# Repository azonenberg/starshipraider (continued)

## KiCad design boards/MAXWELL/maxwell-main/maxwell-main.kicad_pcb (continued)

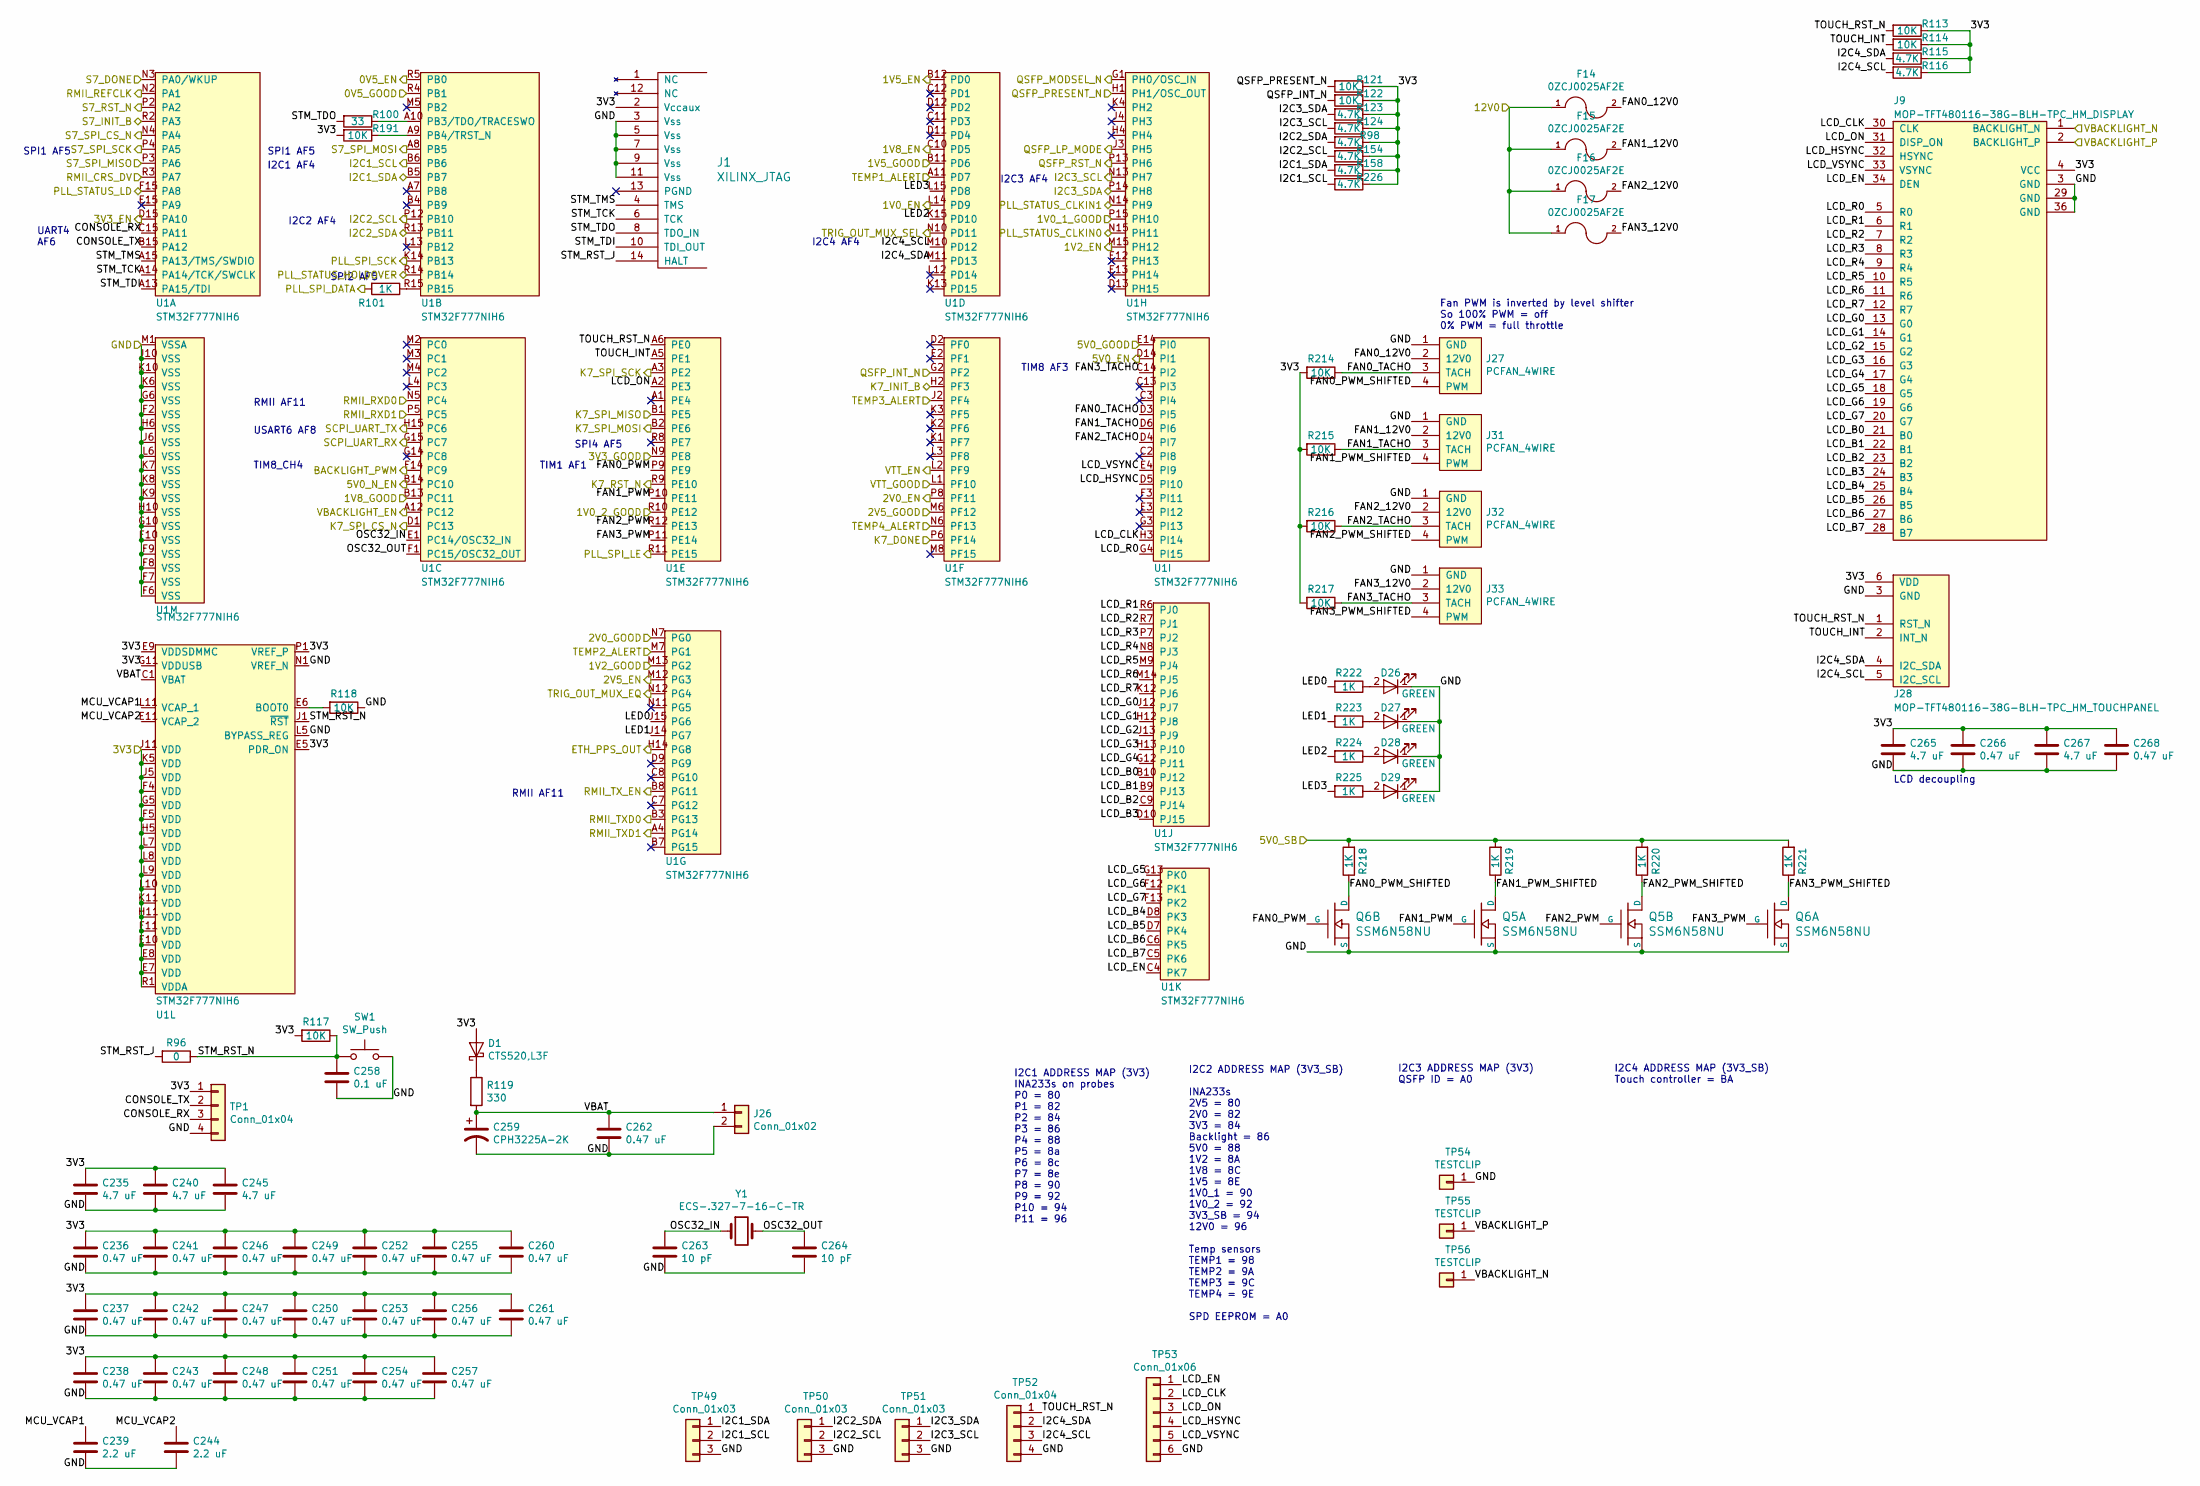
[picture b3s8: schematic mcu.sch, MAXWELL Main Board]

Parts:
C235, C240, C245, C265, C267: 4.7 uF; EIA_0603_CAP_NOSILK
C236, C237, C238, C241, C242, C243, C246, C247, C248, C249, C250, C251, C252, C253, C254, C255, C256, C257, C260, C261, C262, C266, C268: 0.47 uF; EIA_0402_CAP_NOSILK
C239, C244: 2.2 uF; EIA_0603_CAP_NOSILK
C258: 0.1 uF; EIA_0402_CAP_NOSILK
C259: CPH3225A-2K; CAP_SEIKO_CPH3225A
C263, C264: 10 pF; EIA_0402_CAP_NOSILK
D1: CTS520,L3F; SOD882
D26, D27, D28, D29: GREEN; EIA_0603_LED
F14, F15, F16, F17: 0ZCJ0025AF2E; EIA_1206_FUSE_NOSILK
J1: XILINX_JTAG; XILINX_JTAG_PTH_MOLEX_0878311420
J9: MOP-TFT480116-38G-BLH-TPC_HM_DISPLAY; CONN_FFC_0.5MM_1x40_H125755CT-ND
J26: Conn_01x02; CONN_HEADER_2.54MM_1x2
J27, J31, J32, J33: PCFAN_4WIRE; CONN_MOLEX_KK_22-23-2041
J28: MOP-TFT480116-38G-BLH-TPC_HM_TOUCHPANEL; CONN_FFC_0.5MM_1x6_H125773CT-ND
Q5, Q6: SSM6N58NU; DFN_6_0.65MM_2x2MM_GDS
R96: 0; EIA_0402_RES_NOSILK
R98, R115, R116, R123, R124, R154, R158, R226: 4.7K; EIA_0402_RES_NOSILK
R100: 33; EIA_0402_RES_NOSILK
R101, R218, R219, R220, R221, R222, R223, R224, R225: 1K; EIA_0402_RES_NOSILK
R113, R114, R117, R118, R121, R122, R191, R214, R215, R216, R217: 10K; EIA_0402_RES_NOSILK
R119: 330; EIA_0402_RES_NOSILK
SW1: SW_Push; SWITCH_RAFI_MICON_5
TP1, TP52: Conn_01x04; CONN_HEADER_2.54MM_1x4
TP49, TP50, TP51: Conn_01x03; CONN_HEADER_2.54MM_1x3
TP53: Conn_01x06; CONN_HEADER_2.54MM_1x6
TP54, TP55, TP56: TESTCLIP; TESTPOINT_SMT_KEYSTONE_5016
U1: STM32F777NIH6; BGA_216_13x13_DEPOP3x3_0.8MM
Y1: ECS-.327-7-16-C-TR; CRYSTAL_1.6x1.0MM

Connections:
/3V3_SB: C235.1, C236.1, C237.1, C238.1, C240.1, C241.1, C242.1, C243.1, C245.1, C246.1, C247.1, C248.1, C249.1, C250.1, C251.1, C252.1, C253.1, C254.1, C255.1, C256.1, C257.1, C260.1, C261.1, C265.1, C266.1, C267.1, C268.1, D1.2 (A), J1.2 (Vccaux), J9.4 (VCC), J28.6 (VDD), R98.1, R113.1, R114.1, R115.1, R116.1, R117.2, R121.1, R122.1, R123.1, R124.1, R154.1, R158.1, R191.2, R214.2, R215.2, R216.2, R217.2, R226.1, TP1.1, U1.E5 (PDR_ON), U1.E7 (VDD), U1.E8 (VDD), U1.E9 (VDDSDMMC), U1.E10 (VDD), U1.F4 (VDD), U1.F5 (VDD), U1.F11 (VDD), U1.G5 (VDD), U1.G11 (VDDUSB), U1.H5 (VDD), U1.H11 (VDD), U1.J5 (VDD), U1.J11 (VDD), U1.K5 (VDD), U1.K11 (VDD), U1.L7 (VDD), U1.L8 (VDD), U1.L9 (VDD), U1.L10 (VDD), U1.P1 (VREF_P), U1.R1 (VDDA); also elsewhere on the board
/5V0_SB: R218.2, R219.2, R220.2, R221.2; also elsewhere on the board
/12V0: F14.1, F15.1, F16.1, F17.1; also elsewhere on the board
/GND: C235.2, C236.2, C237.2, C238.2, C239.2, C240.2, C241.2, C242.2, C243.2, C244.2, C245.2, C246.2, C247.2, C248.2, C249.2, C250.2, C251.2, C252.2, C253.2, C254.2, C255.2, C256.2, C257.2, C258.2, C259.2, C260.2, C261.2, C262.2, C263.2, C264.2, C265.2, C266.2, C267.2, C268.2, D26.1 (K), D27.1 (K), D28.1 (K), D29.1 (K), J1.3 (Vss), J1.5 (Vss), J1.7 (Vss), J1.9 (Vss), J1.11 (Vss), J9.3 (GND), J9.29 (GND), J9.36 (GND), J26.2, J27.1 (GND), J28.3 (GND), J31.1 (GND), J32.1 (GND), J33.1 (GND), Q5.S1 (S), Q5.S2 (S), Q6.S1 (S), Q6.S2 (S), R118.1, SW1.2, TP1.4, TP49.3, TP50.3, TP51.3, TP52.4, TP53.6, TP54.1, U1.F2 (VSS), U1.F6 (VSS), U1.F7 (VSS), U1.F8 (VSS), U1.F9 (VSS), U1.F10 (VSS), U1.G6 (VSS), U1.G10 (VSS), U1.H6 (VSS), U1.H10 (VSS), U1.J6 (VSS), U1.J10 (VSS), U1.K6 (VSS), U1.K7 (VSS), U1.K8 (VSS), U1.K9 (VSS), U1.K10 (VSS), U1.L5 (BYPASS_REG), U1.L6 (VSS), U1.M1 (VSSA), U1.N1 (VREF_N); also elsewhere on the board
/I2C2_SCL: R154.2, TP50.2, U1.P12 (PB10); also elsewhere on the board
/I2C2_SDA: R98.2, TP50.1, U1.R13 (PB11); also elsewhere on the board
/I2C3_SCL: R124.2, TP51.2, U1.N13 (PH7); also elsewhere on the board
/I2C3_SDA: R123.2, TP51.1, U1.P14 (PH8); also elsewhere on the board
/Inputs/I2C1_SCL: R226.2, TP49.2, U1.B6; also elsewhere on the board
/Inputs/I2C1_SDA: R158.2, TP49.1, U1.B5 (PB7); also elsewhere on the board
/Inputs/S7_DONE: U1.N3 (PA0/WKUP); also elsewhere on the board
/Inputs/S7_INIT_B: U1.R2 (PA3); also elsewhere on the board
/Inputs/S7_RST_N: U1.P2 (PA2); also elsewhere on the board
/Inputs/S7_SPI_CS_N: U1.N4 (PA4); also elsewhere on the board
/Inputs/S7_SPI_MISO: U1.P3 (PA6); also elsewhere on the board
/Inputs/S7_SPI_MOSI: U1.A8 (PB5); also elsewhere on the board
/Inputs/S7_SPI_SCK: U1.P4 (PA5); also elsewhere on the board
/K7_DONE: U1.P6 (PF14); also elsewhere on the board
/K7_INIT_B: U1.H2 (PF3); also elsewhere on the board
/K7_RST_N: U1.R9 (PE10); also elsewhere on the board
/MCU/0V5_EN: U1.R5 (PB0); also elsewhere on the board
/MCU/0V5_GOOD: U1.R4 (PB1); also elsewhere on the board
/MCU/1V0_1_GOOD: U1.P15 (PH10); also elsewhere on the board
/MCU/1V0_2_GOOD: U1.R10 (PE12); also elsewhere on the board
/MCU/1V0_EN: U1.L14 (PD9); also elsewhere on the board
/MCU/1V2_EN: U1.M15 (PH12); also elsewhere on the board
/MCU/1V2_GOOD: U1.M13 (PG2); also elsewhere on the board
/MCU/1V5_EN: U1.B12 (PD0); also elsewhere on the board
/MCU/1V5_GOOD: U1.B11 (PD6); also elsewhere on the board
/MCU/1V8_EN: U1.C10 (PD5); also elsewhere on the board
/MCU/1V8_GOOD: U1.B13 (PC11); also elsewhere on the board
/MCU/2V0_EN: U1.P8 (PF11); also elsewhere on the board
/MCU/2V0_GOOD: U1.N7 (PG0); also elsewhere on the board
/MCU/2V5_EN: U1.M12 (PG3); also elsewhere on the board
/MCU/2V5_GOOD: U1.M6 (PF12); also elsewhere on the board
/MCU/3V3_EN: U1.D15 (PA10); also elsewhere on the board
/MCU/3V3_GOOD: U1.N9 (PE8); also elsewhere on the board
/MCU/5V0_EN: U1.D14 (PI1); also elsewhere on the board
/MCU/5V0_GOOD: U1.E14 (PI0); also elsewhere on the board
/MCU/5V0_N_EN: U1.B14 (PC10); also elsewhere on the board
/MCU/BACKLIGHT_PWM: U1.F14 (PC9); also elsewhere on the board
/MCU/CONSOLE_RX: TP1.3, U1.C15 (PA11)
/MCU/CONSOLE_TX: TP1.2, U1.B15 (PA12)
/MCU/ETH_PPS_OUT: U1.H14 (PG8); also elsewhere on the board
/MCU/FAN0_12V0: F14.2, J27.2 (12V0)
/MCU/FAN0_PWM: Q6.G2 (G), U1.P9 (PE9)
/MCU/FAN0_PWM_SHIFTED: J27.4 (PWM), Q6.D2 (D), R218.1
/MCU/FAN0_TACHO: J27.3 (TACH), R214.1, U1.D3 (PI5)
/MCU/FAN1_12V0: F15.2, J31.2 (12V0)
/MCU/FAN1_PWM: Q5.G1 (G), U1.P10 (PE11)
/MCU/FAN1_PWM_SHIFTED: J31.4 (PWM), Q5.D1 (D), R219.1
/MCU/FAN1_TACHO: J31.3 (TACH), R215.1, U1.D6 (PI6)
/MCU/FAN2_12V0: F16.2, J32.2 (12V0)
/MCU/FAN2_PWM: Q5.G2 (G), U1.R12 (PE13)
/MCU/FAN2_PWM_SHIFTED: J32.4 (PWM), Q5.D2 (D), R220.1
/MCU/FAN2_TACHO: J32.3 (TACH), R216.1, U1.D4 (PI7)
/MCU/FAN3_12V0: F17.2, J33.2 (12V0)
/MCU/FAN3_PWM: Q6.G1 (G), U1.P11 (PE14)
/MCU/FAN3_PWM_SHIFTED: J33.4 (PWM), Q6.D1 (D), R221.1
/MCU/FAN3_TACHO: J33.3 (TACH), R217.1, U1.C14 (PI2)
/MCU/I2C4_SCL: J28.5 (I2C_SCL), R116.2, TP52.3, U1.M10 (PD12)
/MCU/I2C4_SDA: J28.4 (I2C_SDA), R115.2, TP52.2, U1.M11 (PD13)
/MCU/K7_SPI_CS_N: U1.D1 (PC13); also elsewhere on the board
/MCU/K7_SPI_MISO: U1.B1 (PE5); also elsewhere on the board
/MCU/K7_SPI_MOSI: U1.B2 (PE6); also elsewhere on the board
/MCU/K7_SPI_SCK: U1.A3 (PE2); also elsewhere on the board
/MCU/LCD_B0: J9.21 (B0), U1.B10 (PJ12)
/MCU/LCD_B1: J9.22 (B1), U1.B9 (PJ13)
/MCU/LCD_B2: J9.23 (B2), U1.C9 (PJ14)
/MCU/LCD_B3: J9.24 (B3), U1.D10 (PJ15)
/MCU/LCD_B4: J9.25 (B4), U1.D8 (PK3)
/MCU/LCD_B5: J9.26 (B5), U1.D7 (PK4)
/MCU/LCD_B6: J9.27 (B6), U1.C6 (PK5)
/MCU/LCD_B7: J9.28 (B7), U1.C5 (PK6)
/MCU/LCD_CLK: J9.30 (CLK), TP53.2, U1.H3 (PI14)
/MCU/LCD_EN: J9.34 (DEN), TP53.1, U1.C4 (PK7)
/MCU/LCD_G0: J9.13 (G0), U1.J12 (PJ7)
/MCU/LCD_G1: J9.14 (G1), U1.H12 (PJ8)
/MCU/LCD_G2: J9.15 (G2), U1.J13 (PJ9)
/MCU/LCD_G3: J9.16 (G3), U1.H13 (PJ10)
/MCU/LCD_G4: J9.17 (G4), U1.G12 (PJ11)
/MCU/LCD_G5: J9.18 (G5), U1.G13 (PK0)
/MCU/LCD_G6: J9.19 (G6), U1.F12 (PK1)
/MCU/LCD_G7: J9.20 (G7), U1.F13 (PK2)
/MCU/LCD_HSYNC: J9.32 (HSYNC), TP53.4, U1.D5 (PI10)
/MCU/LCD_ON: J9.31 (DISP_ON), TP53.3, U1.A2 (PE3)
/MCU/LCD_R0: J9.5 (R0), U1.G4 (PI15)
/MCU/LCD_R1: J9.6 (R1), U1.R6 (PJ0)
/MCU/LCD_R2: J9.7 (R2), U1.R7 (PJ1)
/MCU/LCD_R3: J9.8 (R3), U1.P7 (PJ2)
/MCU/LCD_R4: J9.9 (R4), U1.N8 (PJ3)
/MCU/LCD_R5: J9.10 (R5), U1.M9 (PJ4)
/MCU/LCD_R6: J9.11 (R6), U1.M14 (PJ5)
/MCU/LCD_R7: J9.12 (R7), U1.K12 (PJ6)
/MCU/LCD_VSYNC: J9.33 (VSYNC), TP53.5, U1.E4 (PI9)
/MCU/LED0: R222.2, U1.J15 (PG6)
/MCU/LED1: R223.2, U1.J14 (PG7)
/MCU/LED2: R224.2, U1.K15 (PD10)
/MCU/LED3: R225.2, U1.L15 (PD8)
/MCU/MCU_VCAP1: C239.1, U1.L11 (VCAP_1)
/MCU/MCU_VCAP2: C244.1, U1.E11 (VCAP_2)
/MCU/OSC32_IN: C263.1, U1.E1 (PC14/OSC32_IN), Y1.1
/MCU/OSC32_OUT: C264.1, U1.F1 (PC15/OSC32_OUT), Y1.2
/MCU/RMII_CRS_DV: U1.R3 (PA7); also elsewhere on the board
/MCU/RMII_REFCLK: U1.N2 (PA1); also elsewhere on the board
/MCU/RMII_RXD0: U1.N5 (PC4); also elsewhere on the board
/MCU/RMII_RXD1: U1.P5 (PC5); also elsewhere on the board
/MCU/RMII_TXD0: U1.B3 (PG13); also elsewhere on the board
/MCU/RMII_TXD1: U1.A4 (PG14); also elsewhere on the board
/MCU/RMII_TX_EN: U1.B8 (PG11); also elsewhere on the board
/MCU/STM_RST_J: J1.14 (HALT), R96.2
/MCU/STM_RST_N: C258.1, R96.1, R117.1, SW1.1, U1.J1 (~RST)
/MCU/STM_TCK: J1.6 (TCK), U1.A14 (PA14/TCK/SWCLK)
/MCU/STM_TDI: J1.10 (TDI_OUT), U1.A13 (PA15/TDI)
/MCU/STM_TDO: J1.8 (TDO_IN), R100.2
/MCU/STM_TMS: J1.4 (TMS), U1.A15 (PA13/TMS/SWDIO)
/MCU/TOUCH_INT: J28.2 (INT_N), R114.2, U1.A5 (PE1)
/MCU/TOUCH_RST_N: J28.1 (RST_N), R113.2, TP52.1, U1.A6 (PE0)
/MCU/VBACKLIGHT_EN: U1.A12 (PC12); also elsewhere on the board
/MCU/VBAT: C259.1, C262.1, J26.1, R119.2, U1.C1 (VBAT)
/MCU/VTT_EN: U1.L2 (PF9); also elsewhere on the board
/MCU/VTT_GOOD: U1.L1 (PF10); also elsewhere on the board
/PLL_SPI_CLK: U1.K14 (PB13); also elsewhere on the board
/PLL_SPI_DATA: R101.2; also elsewhere on the board
/PLL_SPI_LE: U1.R11 (PE15); also elsewhere on the board
/PLL_STATUS_CLKIN0: U1.N15 (PH11); also elsewhere on the board
/PLL_STATUS_CLKIN1: U1.N14 (PH9); also elsewhere on the board
/PLL_STATUS_HOLDOVER: U1.R14 (PB14); also elsewhere on the board
/PLL_STATUS_LD: U1.F15 (PA8); also elsewhere on the board
/QSFP_INT_N: R122.2, U1.G2 (PF2); also elsewhere on the board
/QSFP_LP_MODE: U1.J3 (PH5); also elsewhere on the board
/QSFP_MODSEL_N: U1.G1 (PH0/OSC_IN); also elsewhere on the board
/QSFP_PRESENT_N: R121.2, U1.H1 (PH1/OSC_OUT); also elsewhere on the board
/QSFP_RST_N: U1.P13 (PH6); also elsewhere on the board
/SCPI_UART_RX: U1.G15 (PC7); also elsewhere on the board
/SCPI_UART_TX: U1.H15 (PC6); also elsewhere on the board
/TEMP1_ALERT: U1.A11 (PD7); also elsewhere on the board
/TEMP2_ALERT: U1.M7 (PG1); also elsewhere on the board
/TEMP3_ALERT: U1.J2 (PF4); also elsewhere on the board
/TEMP4_ALERT: U1.N6 (PF13); also elsewhere on the board
/TRIG_OUT_MUX_EQ: U1.N12 (PG4); also elsewhere on the board
/TRIG_OUT_SEL: U1.N10 (PD11); also elsewhere on the board
/VBACKLIGHT_N: J9.1 (BACKLIGHT_N), TP56.1; also elsewhere on the board
/VBACKLIGHT_P: J9.2 (BACKLIGHT_P), TP55.1; also elsewhere on the board
unnamed: D1.1 (K), R119.1
unnamed: D26.2 (A), R222.1
unnamed: D27.2 (A), R223.1
unnamed: D28.2 (A), R224.1
unnamed: D29.2 (A), R225.1
unnamed: R100.1, U1.A10 (PB3/TDO/TRACESWO)
unnamed: R101.1, U1.R15 (PB15)
unnamed: R118.2, U1.E6 (BOOT0)
unnamed: R191.1, U1.A9 (PB4/TRST_N)

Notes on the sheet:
SPI1 AF5
SPI2 AF5
I2C1 AF4
I2C2 AF4
I2C4 AF4
LCD decoupling
UART4 AF6
USART6 AF8
I2C3 AF4
I2C2 ADDRESS MAP (3V3_SB) INA233s 2V5 = 80 2V0 = 82 3V3 = 84 Backlight = 86 5V0 = 88 1V2 = 8A 1V8 = 8C 1V5 = 8E 1V0_1 = 90 1V0_2 = 92 3V3_SB = 94 12V0 = 96 Temp sensors TEMP1 = 98 TEMP2 = 9A TEMP3 = 9C TEMP4 = 9E SPD EEPROM = A0
I2C3 ADDRESS MAP (3V3) QSFP ID = A0
I2C4 ADDRESS MAP (3V3_SB) Touch controller = BA
TIM8_CH4
I2C1 ADDRESS MAP (3V3) INA233s on probes P0 = 80 P1 = 82 P2 = 84 P3 = 86 P4 = 88 P5 = 8a P6 = 8c P7 = 8e P8 = 90 P9 = 92 P10 = 94 P11 = 96
RMII AF11
SPI4 AF5
TIM1 AF1
TIM8 AF3
Fan PWM is inverted by level shifter So 100% PWM = off 0% PWM = full throttle

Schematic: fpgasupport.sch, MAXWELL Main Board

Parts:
C137, C144: 330 uF; EIA_1210_CAP_NOSILK
C138, C142, C143: 100 uF; EIA_1210_CAP_NOSILK
C139, C140, C146: 47 uF; EIA_0805_CAP_NOSILK
C141: 47 uF; EIA_1210_CAP_NOSILK
C145, C147, C148, C149, C150, C151, C152, C153, C154, C158, C159, C160, C164: 4.7 uF; EIA_0603_CAP_NOSILK
C155, C156, C157, C161, C162, C163: 22 uF; EIA_0805_CAP_NOSILK
C165: 0.47 uF; EIA_0402_CAP_NOSILK
FB22, FB23, FB24: 300R; EIA_2220_INDUCTOR
J10: XILINX_JTAG; XILINX_JTAG_PTH_MOLEX_0878311420
R54, R55, R57, R58, R59, R60, R61: 33; EIA_0402_RES_NOSILK
R56, R245, R246, R247: 4.7K; EIA_0402_RES_NOSILK
TP57, TP58, TP59, TP60, TP61, TP62, TP63, TP64, TP65, TP66, TP67, TP68, TP69, TP70, TP71, TP72, TP73: TESTCLIP; TESTPOINT_SMT_KEYSTONE_5016
TP74, TP75, TP76: TESTPAD; TESTPOINT_SMT_0.5MM
U2: XC7K160T-2FFG676C; BGA_676_27x27_FULLARRAY_1MM_FFG676
U34: S25FL128LAGNFV010; DFN_8_1.27MM_6x5MM

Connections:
/1V0_1: C137.1, C138.1, C144.1, C145.1, C147.1, C148.1, TP57.1, U2.J9 (VCCINT), U2.K8 (VCCINT), U2.K10 (VCCINT), U2.K12 (VCCINT), U2.K14 (VCCINT), U2.L9 (VCCINT), U2.L13 (VCCINT), U2.L15 (VCCINT), U2.M8 (VCCINT), U2.M14 (VCCINT), U2.N9 (VCCINT), U2.N13 (VCCBRAM), U2.N15 (VCCINT), U2.P14 (VCCINT), U2.R13 (VCCBRAM), U2.R15 (VCCINT), U2.T12 (VCCBRAM), U2.T14 (VCCINT), U2.U13 (VCCBRAM), U2.U15 (VCCINT); also elsewhere on the board
/1V0_2: C155.1, C158.1, FB22.2; also elsewhere on the board
/1V2: C156.1, C159.1, FB23.2, TP66.1; also elsewhere on the board
/1V5: C142.1, TP60.1, U2.AA1 (VCCO_34), U2.AA11 (VCCO_33), U2.AB8 (VCCO_33), U2.AB18 (VCCO_32), U2.AC5 (VCCO_34), U2.AC15 (VCCO_32), U2.AD2 (VCCO_34), U2.AD12 (VCCO_33), U2.AE9 (VCCO_33), U2.AE19 (VCCO_32), U2.AF6 (VCCO_34), U2.AF16 (VCCO_32), U2.U3 (VCCO_34), U2.V10 (VCCO_33), U2.W7 (VCCO_33), U2.W17 (VCCO_32), U2.Y4 (VCCO_34), U2.Y14 (VCCO_32); also elsewhere on the board
/1V8: C139.1, C146.1, C157.1, C160.1, FB24.2, TP58.1, TP67.1, U2.E8 (VCCBATT_0), U2.L11 (VCCAUX), U2.M10 (VCCAUX), U2.M12 (VCCADC_0), U2.P10 (VCCAUX), U2.T10 (VCCAUX), U2.U11 (VCCAUX); also elsewhere on the board
/2V0: C140.1, TP59.1, U2.P8 (VCCAUX_IO_G0), U2.R9 (VCCAUX_IO_G0), U2.T8 (VCCAUX_IO_G0); also elsewhere on the board
/2V5: C143.1, TP62.1, U2.A11 (VCCO_16), U2.AA21 (VCCO_12), U2.AC25 (VCCO_12), U2.AD22 (VCCO_12), U2.AF26 (VCCO_12), U2.B8 (VCCO_16), U2.B18 (VCCO_15), U2.C15 (VCCO_16), U2.D12 (VCCO_16), U2.E9 (VCCO_16), U2.E19 (VCCO_15), U2.F16 (VCCO_15), U2.G13 (VCCO_16), U2.H10 (VCCO_16), U2.H20 (VCCO_15), U2.J17 (VCCO_15), U2.K24 (VCCO_13), U2.M18 (VCCO_15), U2.N25 (VCCO_13), U2.P22 (VCCO_13), U2.R19 (VCCO_13), U2.T16 (VCCO_13), U2.T26 (VCCO_13), U2.U23 (VCCO_12), U2.V20 (VCCO_12), U2.Y24 (VCCO_12); also elsewhere on the board
/3V3: C141.1, C164.1, C165.1, J10.2 (Vccaux), R56.1, R57.1, R245.1, R246.1, R247.1, TP61.1, U2.A21 (VCCO_14), U2.C25 (VCCO_14), U2.D22 (VCCO_14), U2.F26 (VCCO_14), U2.G23 (VCCO_14), U2.L7 (VCCO_0), U2.L21 (VCCO_14), U2.P7 (CFGBVS_0), U2.T5 (M0_0), U2.T6 (VCCO_0), U34.8 (VCC); also elsewhere on the board
/FPGA Support/GTX_1V0: C149.1, C152.1, C161.1, FB22.1, TP63.1, U2.C6 (MGTAVCC), U2.E6 (MGTAVCC), U2.G6 (MGTAVCC), U2.J6 (MGTAVCC), U2.L6 (MGTAVCC)
/FPGA Support/GTX_1V8: C151.1, C154.1, C163.1, FB24.1, TP65.1, U2.N6 (MGTVCCAUX)
/FPGA Support/K7_QSPI_SCK: R55.2, U34.6 (CLK)
/FPGA Support/K7_TCK: J10.6 (TCK), U2.L8 (TCK_0)
/FPGA Support/K7_TDI: J10.10 (TDI_OUT), U2.R6 (TDI_0)
/FPGA Support/K7_TDO: J10.8 (TDO_IN), R54.2
/FPGA Support/K7_TMS: J10.4 (TMS), U2.N8 (TMS_0)
/GND: C137.2, C138.2, C139.2, C140.2, C141.2, C142.2, C143.2, C144.2, C145.2, C146.2, C147.2, C148.2, C149.2, C150.2, C151.2, C152.2, C153.2, C154.2, C164.2, C165.2, J10.3 (Vss), J10.5 (Vss), J10.7 (Vss), J10.9 (Vss), J10.11 (Vss), TP68.1, TP69.1, TP70.1, TP71.1, TP72.1, TP73.1, U2.A1 (GND), U2.A2 (GND), U2.A5 (GND), U2.A6 (GND), U2.A7 (GND), U2.A16 (GND), U2.A26 (GND), U2.AA6 (GND), U2.AA16 (GND), U2.AA26 (GND), U2.AB3 (GND), U2.AB13 (GND), U2.AB23 (GND), U2.AC10 (GND), U2.AC20 (GND), U2.AD7 (GND), U2.AD17 (GND), U2.AE4 (GND), U2.AE14 (GND), U2.AE24 (GND), U2.AF1 (GND), U2.AF11 (GND), U2.AF21 (GND), U2.B4 (GND), U2.B7 (GND), U2.B13 (GND), U2.B23 (GND), U2.C1 (GND), U2.C5 (GND), U2.C7 (GND), U2.C10 (GND), U2.C20 (GND), U2.D4 (GND), U2.D7 (GND), U2.D17 (GND), U2.E1 (GND), U2.E2 (GND), U2.E5 (GND), U2.E7 (GND), U2.E14 (GND), U2.E24 (GND), U2.F3 (GND), U2.F4 (GND), U2.F7 (GND), U2.F11 (GND), U2.F21 (GND), U2.G1 (GND), U2.G5 (GND), U2.G8 (GND), U2.G18 (GND), U2.H4 (GND), U2.H7 (GND), U2.H15 (GND), U2.H25 (GND), U2.J1 (GND), U2.J2 (GND), U2.J5 (GND), U2.J12 (GND), U2.J22 (GND), U2.K3 (GND), U2.K4 (GND), U2.K7 (GND), U2.K9 (GND), U2.K11 (GND), U2.K13 (GND), U2.K19 (GND), U2.L1 (GND), U2.L5 (GND), U2.L10 (GND), U2.L12 (GND), U2.L14 (GND), U2.L16 (GND), U2.L26 (GND), U2.M4 (GND), U2.M7 (GND), U2.M9 (GND), U2.M11 (GNDADC_0), U2.M13 (GND), U2.M15 (GND), U2.M23 (GND), U2.N1 (GND), U2.N2 (GND), U2.N5 (GND), U2.N7 (GND), U2.N10 (GND), U2.N11 (VREFN_0), U2.N12 (VP_0), U2.N14 (GND), U2.N20 (GND), U2.P3 (GND), U2.P4 (GND), U2.P5 (M2_0), U2.P9 (GND), U2.P11 (VN_0), U2.P12 (VREFP_0), U2.P13 (GND), U2.P15 (GND), U2.P17 (GND), U2.R1 (GND), U2.R2 (GND), U2.R5 (GND), U2.R8 (GND), U2.R10 (GND), U2.R11 (DXN_0), U2.R12 (DXP_0), U2.R14 (GND), U2.R24 (GND), U2.T1 (GND), U2.T2 (M1_0), U2.T3 (GND), U2.T4 (GND), U2.T9 (GND), U2.T11 (GND), U2.T13 (GND), U2.T15 (GND), U2.T21 (GND), U2.U8 (GND), U2.U10 (GND), U2.U12 (GND), U2.U14 (GND), U2.U18 (GND), U2.V5 (GND), U2.V15 (GND), U2.V25 (GND), U2.W2 (GND), U2.W12 (GND), U2.W22 (GND), U2.Y9 (GND), U2.Y19 (GND), U34.4 (GND); also elsewhere on the board
/GTX_1V2: C150.1, C153.1, C162.1, FB23.1, TP64.1, U2.B3 (MGTAVTT), U2.C2 (MGTAVTT), U2.D3 (MGTAVTT), U2.G2 (MGTAVTT), U2.H3 (MGTAVTT), U2.L2 (MGTAVTT), U2.M3 (MGTAVTT); also elsewhere on the board
/K7_DONE: TP76.1, U2.J7 (DONE_0); also elsewhere on the board
/K7_INIT_B: R56.2, TP74.1, U2.G7 (INIT_B_0); also elsewhere on the board
/K7_QSPI_CS_N: R245.2, U34.1 (CS#); also elsewhere on the board
/K7_QSPI_DQ0: R61.1; also elsewhere on the board
/K7_QSPI_DQ1: R58.2; also elsewhere on the board
/K7_QSPI_DQ2: R59.2, R246.2; also elsewhere on the board
/K7_QSPI_DQ3: R60.1, R247.2; also elsewhere on the board
/K7_RST_N: R57.2, TP75.1, U2.P6 (PROGRAM_B_0); also elsewhere on the board
unnamed: C155.2, C158.2, C161.2
unnamed: C156.2, C159.2, C162.2
unnamed: C157.2, C160.2, C163.2
unnamed: R54.1, U2.R7 (TDO_0)
unnamed: R55.1, U2.C8 (CCLK_0)
unnamed: R58.1, U34.2 (DO/IO1)
unnamed: R59.1, U34.3 (WP#/IO2)
unnamed: R60.2, U34.7 (HOLD#/IO3)
unnamed: R61.2, U34.5 (DI/IO0)

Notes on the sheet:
Total 10 mV p-p max on GTX rails Need filter networks
VCCINT decoupling
VCCBRAM decoupling
VCCAUX decoupling
VCCAUX_IO decoupling
VCCO_0/14 decoupling
VCCO_32/33/34 decoupling
VCCO_12/13/15/16 decoupling
GTX decoupling

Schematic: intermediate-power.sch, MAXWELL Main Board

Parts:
C106: 100 uF 63V; CAP_AL_10MM_SMT
C282: 100 uF 25V; CAP_AL_6.3MM_SMT
C323: 4.7 uF 25V; EIA_0805_CAP_NOSILK
C324: 1 uF; EIA_0603_CAP_NOSILK
C339: 22 uF 25V; EIA_1210_CAP_NOSILK
C340: 22 uF; EIA_0805_CAP_NOSILK
C341: DNP; EIA_1206_CAP_NOSILK
C403, C408: 0.47 uF; EIA_0402_CAP_NOSILK
F13: 10A; EIA_1206_FUSE_NOSILK
FL1: BNX003-11
J24: VES180_MINIFITJR; CONN_MOLEX_MINIFITJR_39-30-1080
R171: 2.2K 1%; EIA_0402_RES_NOSILK
R172: 10K; EIA_0402_RES_NOSILK
R205: LVK12R012FER; OHMITE_LVK12
R206: LVK25R002FER; OHMITE_LVK25
SW2: SW_SPST; CONN_HEADER_2.54MM_1x2
TP2: TESTPAD; TESTPOINT_SMT_0.5MM
U52: E36SC12009NRFA; MODULE_DCDC_DOSA_EIGHTHBRICK
U56: MCP1755S-DFN; DFN_8_0.5MM_2x3MM_TALL
U60: OKL-T/3-W12P-C; MODULE_MURATA_OKL-T3-W12
U79, U84: INA233; SOP_10_0.5MM_3MM

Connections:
/3V3_SB: C403.1, C408.1, R205.2 (Vo), U60.5 (SENSE), U79.6 (Vs+), U79.8 (Vbus), U84.6 (Vs+); also elsewhere on the board
/5V0_SB: C324.1, R172.2, U56.1 (VOUT); also elsewhere on the board
/12V0: C323.1, C339.1, R206.2 (Vo), U52.7 (SENSE+), U56.8 (VIN), U60.1 (EN), U60.2 (VIN), U60.9 (SEQ/TRK), U84.8 (Vbus); also elsewhere on the board
/GND: C106.2, C282.2, C323.2, C324.2, C339.2, C340.2, C341.2, C403.2, C408.2, FL1.4 (GND_OUT), R171.2, SW2.1 (A), U52.3 (GND_IN), U52.4 (GND_OUT), U52.5 (SENSE-), U56.4 (GND), U56.PAD (GND), U60.3 (GND), U60.7 (GND), U79.7 (GND), U84.7 (GND); also elsewhere on the board
/I2C2_SCL: U79.5 (SCL), U84.2 (A0), U84.5 (SCL); also elsewhere on the board
/I2C2_SDA: U79.1 (A1), U79.2 (A0), U79.4 (SDA), U84.1 (A1), U84.4 (SDA); also elsewhere on the board
/Power Supply/Intermediate and Standby Rails/3V3_SB_GOOD: R172.1, TP2.1, U60.10 (PGOOD)
/Power Supply/Intermediate and Standby Rails/3V3_SB_SENSE_HI: R205.3 (Ihi), U79.10 (Vin+)
/Power Supply/Intermediate and Standby Rails/3V3_SB_SENSE_LO: R205.1 (Ilo), U79.9 (Vin-)
/Power Supply/Intermediate and Standby Rails/12V0_ON_N: SW2.2 (B), U52.2 (ON/OFF)
/Power Supply/Intermediate and Standby Rails/12V0_SENSE_HI: R206.3 (Ihi), U84.10 (Vin+)
/Power Supply/Intermediate and Standby Rails/12V0_SENSE_LO: R206.1 (Ilo), U84.9 (Vin-)
/Power Supply/Intermediate and Standby Rails/GND_IN: FL1.3 (GND_IN), J24.1 (GND), J24.2 (GND), J24.3 (GND), J24.4 (GND)
/Power Supply/Intermediate and Standby Rails/VIN: F13.1, J24.5 (VIN), J24.6 (VIN), J24.7 (VIN), J24.8 (VIN)
/Power Supply/Intermediate and Standby Rails/VIN_FILT: C106.1, FL1.2 (PWR_OUT), U52.1 (VIN)
/Power Supply/Intermediate and Standby Rails/VIN_FUSED: F13.2, FL1.1 (PWR_IN)
unnamed: C282.1, R206.4 (Vi), U52.8 (VOUT)
unnamed: C340.1, C341.1, R205.4 (Vi), U60.4 (VOUT)
unnamed: R171.1, U60.6 (TRIM)

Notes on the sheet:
Input is 24V @ 4A or 48V @ 2A. Use 10A fuse to provide some headroom Supply recommends more like 20 for inrush though?
Expected efficiency @ 48V in is ~~93%. Assuming 7.3A load, we'll dissipate a bit under 7W in this module. Overcurrent shutdown at around 11A Converter is isolated, but in/out ground are connected since we don't actually need isolation.
Hard power switch (back side)
5V standby rail is just used to drive enable lines for DC-DC's Doesn't need high current
8'h94
12 mR = 18 mV @ 1.5A 208.333 uA/LSB
8'h96
2 mR = 16 mV @ 8A 1.25 mA/LSB

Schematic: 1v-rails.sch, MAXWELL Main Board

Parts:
C283, C297, C298, C299, C300, C301, C302, C303, C304, C305, C306, C307: 22 uF; EIA_1210_CAP_NOSILK
C308, C309, C310, C311, C312, C313, C314, C315, C316, C317, C318, C319: 47 uF; EIA_1206_CAP_NOSILK
C320, C321, C322, C334: 0.1 uF; EIA_0402_CAP_NOSILK
C325, C326: 22 uF 25V; EIA_1210_CAP_NOSILK
C327, C328: 22 uF; EIA_0805_CAP_NOSILK
C329, C330: DNP; EIA_1206_CAP_NOSILK
C331, C332, C335, C336, C337, C375, C376, C378, C379, C380: 10 uF; EIA_0805_CAP_NOSILK
C333: 1 nF; EIA_0402_CAP_NOSILK
C338, C381: 4.7 uF; EIA_0603_CAP_NOSILK
C377: 1 nF; EIA_0603_CAP_NOSILK
C393, C394, C395, C396, C397: 0.47 uF; EIA_0402_CAP_NOSILK
Q1, Q2: SSM6N58NU; DFN_6_0.65MM_2x2MM_GDS
R151, R152: 22.1K 1%; EIA_0402_RES_NOSILK
R153: 8.45K 1%; EIA_0402_RES_NOSILK
R155, R156, R157: 0; EIA_0402_RES_NOSILK
R159, R160, R161, R162, R163, R164, R165, R166, R239, R240: 10K; EIA_0402_RES_NOSILK
R167, R168: 9.65K 1%; EIA_0402_RES_NOSILK
R169, R170, R186, R187: 10K 1%; EIA_0402_RES_NOSILK
R195, R196, R197: LVK25R005FER; OHMITE_LVK25
R198, R199: LVK12R012FER; OHMITE_LVK12
U53, U54, U55: IAF12020A007V-003-R; MODULE_DCDC_TDK_IAF
U57, U58: OKL-T/3-W12P-C; MODULE_MURATA_OKL-T3-W12
U59, U64: RT9088A; DFN_10_0.5MM_3x3MM
U69, U70, U71, U72, U73: INA233; SOP_10_0.5MM_3MM

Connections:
/0V5: C378.1, C379.1, C380.1, U64.3 (VOUT), U64.5 (SENSE); also elsewhere on the board
/1V0_1: R155.1, R186.1, R195.2 (Vo), U72.8 (Vbus); also elsewhere on the board
/1V0_2: R156.1, R196.2 (Vo), U73.8 (Vbus); also elsewhere on the board
/1V2: R198.2 (Vo), U57.5 (SENSE), U69.8 (Vbus); also elsewhere on the board
/1V5: C331.1, C332.1, C375.1, C376.1, R157.1, R169.1, R197.2 (Vo), U59.2 (VIN), U64.2 (VIN), U71.8 (Vbus); also elsewhere on the board
/1V8: R199.2 (Vo), U58.5 (SENSE), U70.8 (Vbus); also elsewhere on the board
/3V3_SB: C338.1, C381.1, C393.1, C394.1, C395.1, C396.1, C397.1, R163.1, R165.1, U59.10 (VCNTL), U64.10 (VCNTL), U69.1 (A1), U69.2 (A0), U69.6 (Vs+), U70.1 (A1), U70.6 (Vs+), U71.1 (A1), U71.6 (Vs+), U72.6 (Vs+), U73.2 (A0), U73.6 (Vs+); also elsewhere on the board
/5V0_SB: R160.1, R162.1, R164.1, R166.1; also elsewhere on the board
/12V0: C283.1, C297.1, C298.1, C299.1, C300.1, C301.1, C302.1, C303.1, C304.1, C305.1, C306.1, C307.1, C325.1, C326.1, U53.2 (VIN), U53.3 (SEQ), U54.2 (VIN), U54.3 (SEQ), U55.2 (VIN), U55.3 (SEQ), U57.2 (VIN), U57.9 (SEQ/TRK), U58.2 (VIN), U58.9 (SEQ/TRK); also elsewhere on the board
/GND: C283.2, C297.2, C298.2, C299.2, C300.2, C301.2, C302.2, C303.2, C304.2, C305.2, C306.2, C307.2, C308.2, C309.2, C310.2, C311.2, C312.2, C313.2, C314.2, C315.2, C316.2, C317.2, C318.2, C319.2, C320.2, C321.2, C322.2, C325.2, C326.2, C327.2, C328.2, C329.2, C330.2, C331.2, C332.2, C333.2, C334.2, C335.2, C336.2, C337.2, C338.2, C375.2, C376.2, C377.2, C378.2, C379.2, C380.2, C381.2, C393.2, C394.2, C395.2, C396.2, C397.2, Q1.S1 (S), Q1.S2 (S), Q2.S1 (S), Q2.S2 (S), R151.2, R152.2, R153.2, R159.2, R161.2, R167.2, R168.2, R170.2, R187.2, R239.1, R240.1, U53.4 (GND), U54.4 (GND), U55.4 (GND), U57.3 (GND), U57.7 (GND), U58.3 (GND), U58.7 (GND), U59.4 (PGND), U59.8 (GND), U59.PAD (PGND), U64.4 (PGND), U64.8 (GND), U64.PAD (PGND), U69.7 (GND), U70.7 (GND), U71.7 (GND), U72.2 (A0), U72.7 (GND), U73.7 (GND); also elsewhere on the board
/I2C2_SCL: U69.5 (SCL), U70.5 (SCL), U71.2 (A0), U71.5 (SCL), U72.5 (SCL), U73.5 (SCL); also elsewhere on the board
/I2C2_SDA: U69.4 (SDA), U70.2 (A0), U70.4 (SDA), U71.4 (SDA), U72.1 (A1), U72.4 (SDA), U73.1 (A1), U73.4 (SDA); also elsewhere on the board
/MCU/0V5_EN: R240.2, U64.7 (EN); also elsewhere on the board
/MCU/0V5_GOOD: U64.9 (PGOOD); also elsewhere on the board
/MCU/1V0_1_GOOD: U53.9 (PGOOD); also elsewhere on the board
/MCU/1V0_2_GOOD: U54.9 (PGOOD); also elsewhere on the board
/MCU/1V0_EN: Q2.G2 (G), R161.1; also elsewhere on the board
/MCU/1V2_EN: Q2.G1 (G), R163.2; also elsewhere on the board
/MCU/1V2_GOOD: U57.10 (PGOOD); also elsewhere on the board
/MCU/1V5_EN: Q1.G1 (G), R159.1; also elsewhere on the board
/MCU/1V5_GOOD: U55.9 (PGOOD); also elsewhere on the board
/MCU/1V8_EN: Q1.G2 (G), R165.2; also elsewhere on the board
/MCU/1V8_GOOD: U58.10 (PGOOD); also elsewhere on the board
/MCU/VTT_EN: R239.2, U59.7 (EN); also elsewhere on the board
/MCU/VTT_GOOD: U59.9 (PGOOD); also elsewhere on the board
/Power Supply/1.xV rails/1V0_1_RAW: C308.1, C311.1, C314.1, C317.1, C320.1, R195.4 (Vi), U53.5 (VOUT)
/Power Supply/1.xV rails/1V0_1_SENSE: R155.2, U53.7 (SENSE+)
/Power Supply/1.xV rails/1V0_1_SENSE_HI: R195.3 (Ihi), U72.10 (Vin+)
/Power Supply/1.xV rails/1V0_1_SENSE_LO: R195.1 (Ilo), U72.9 (Vin-)
/Power Supply/1.xV rails/1V0_2_RAW: C309.1, C312.1, C315.1, C318.1, C321.1, R196.4 (Vi), U54.5 (VOUT)
/Power Supply/1.xV rails/1V0_2_SENSE: R156.2, U54.7 (SENSE+)
/Power Supply/1.xV rails/1V0_2_SENSE_HI: R196.3 (Ihi), U73.10 (Vin+)
/Power Supply/1.xV rails/1V0_2_SENSE_LO: R196.1 (Ilo), U73.9 (Vin-)
/Power Supply/1.xV rails/1V0_EN_SHIFT: Q2.D2 (D), R162.2, U53.1 (EN), U54.1 (EN)
/Power Supply/1.xV rails/1V2_EN_SHIFT: Q2.D1 (D), R164.2, U57.1 (EN)
/Power Supply/1.xV rails/1V2_SENSE_HI: R198.3 (Ihi), U69.10 (Vin+)
/Power Supply/1.xV rails/1V2_SENSE_LO: R198.1 (Ilo), U69.9 (Vin-)
/Power Supply/1.xV rails/1V5_EN_SHIFT: Q1.D1 (D), R160.2, U55.1 (EN)
/Power Supply/1.xV rails/1V5_RAW: C310.1, C313.1, C316.1, C319.1, C322.1, R197.4 (Vi), U55.5 (VOUT)
/Power Supply/1.xV rails/1V5_SENSE: R157.2, U55.7 (SENSE+)
/Power Supply/1.xV rails/1V5_SENSE_HI: R197.3 (Ihi), U71.10 (Vin+)
/Power Supply/1.xV rails/1V5_SENSE_LO: R197.1 (Ilo), U71.9 (Vin-)
/Power Supply/1.xV rails/1V8_EN_SHIFT: Q1.D2 (D), R166.2, U58.1 (EN)
/Power Supply/1.xV rails/1V8_SENSE_HI: R199.3 (Ihi), U70.10 (Vin+)
/Power Supply/1.xV rails/1V8_SENSE_LO: R199.1 (Ilo), U70.9 (Vin-)
/Power Supply/1.xV rails/5REFIN: C377.1, R186.2, R187.1, U64.1 (REFIN)
/Power Supply/1.xV rails/REFIN: C333.1, R169.2, R170.1, U59.1 (REFIN)
/RAM_VREF: C334.1, U59.6 (REFOUT); also elsewhere on the board
/RAM_VTT: C335.1, C336.1, C337.1, U59.3 (VOUT), U59.5 (SENSE); also elsewhere on the board
unnamed: C327.1, C329.1, R198.4 (Vi), U57.4 (VOUT)
unnamed: C328.1, C330.1, R199.4 (Vi), U58.4 (VOUT)
unnamed: R151.1, U53.6 (TRIM)
unnamed: R152.1, U54.6 (TRIM)
unnamed: R153.1, U55.6 (TRIM)
unnamed: R167.1, U57.6 (TRIM)
unnamed: R168.1, U58.6 (TRIM)

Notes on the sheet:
Suggested C3225X7R1C226MT or equivalent
Dual 1V0 rails, one for GTX and one for FPGA core
Regulator enables need >3.3V to switch on fully: * IAFs need 4.2V min * OKL-T/3 needs 3.5V min Level shifter inverts, drive low to enable 1V2 or 1V8 1V5/1V0 are negative enable so after inversion, drive high to enable
8'h8a
12 mR = 18 mV @ 1.5A 208.333 uA/LSB
8'h8c
8'h8e
5 mR = 30 mV @ 6A 500 uA/LSB
8'h90
8'h92
1.xV rails are max 6A LVK25 are rated for 2W 6A through 5 mR = 180 mW max

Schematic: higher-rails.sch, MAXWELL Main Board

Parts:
C342, C343, C344, C386: 22 uF 25V; EIA_1210_CAP_NOSILK
C345, C346, C347, C387, C388: 22 uF; EIA_1210_CAP_NOSILK
C348, C349, C350: DNP; EIA_1210_CAP_NOSILK
C382, C385: 2.2 uF 50V; EIA_1206_CAP_NOSILK
C383, C384: 0.1 uF 50V; EIA_0603_CAP_NOSILK
C389, C391, C392: 4.7 uF; EIA_0603_CAP_NOSILK
C390: 1 uF; EIA_0603_CAP_NOSILK
C398, C399, C400, C401, C402: 0.47 uF; EIA_0402_CAP_NOSILK
L7: 10 uH; EIA_0805_INDUCTOR_NOSILK
Q3, Q4: SSM6N58NU; DFN_6_0.65MM_2x2MM_GDS
R173, R174, R178, R179, R180, R181, R241, R242, R243: 10K; EIA_0402_RES_NOSILK
R175: 3.09K 1%; EIA_0402_RES_NOSILK
R176: 4.22K 1%; EIA_0402_RES_NOSILK
R177: 2.2K 1%; EIA_0402_RES_NOSILK
R188: 16.2K 1%; EIA_0402_RES_NOSILK
R189: 1K 1%; EIA_0402_RES_NOSILK
R190: 40.2 1%; EIA_0402_RES_NOSILK
R192: 1K; EIA_0402_RES_NOSILK
R193: 287K; EIA_0402_RES_NOSILK
R194: 100K; EIA_0402_RES_NOSILK
R200, R201, R202: LVK12R012FER; OHMITE_LVK12
R203, R204: LVK12R100CER; OHMITE_LVK12
U61, U62, U63: OKL-T/3-W12P-C; MODULE_MURATA_OKL-T3-W12
U65: MIC2605; DFN_8_0.5MM_2x2MM
U66: TSCR421; SOT23_6
U67: RPM5.0-2.0; MODULE_DCDC_RECOM_RPM
U68: LM27761; DFN_8_0.5MM_2x2MM
U74, U75, U76, U77, U78: INA233; SOP_10_0.5MM_3MM

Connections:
/2V0: R201.2 (Vo), U62.5 (SENSE), U75.8 (Vbus); also elsewhere on the board
/2V5: R200.2 (Vo), U61.5 (SENSE), U74.8 (Vbus); also elsewhere on the board
/3V3: R202.2 (Vo), U63.5 (SENSE), U76.8 (Vbus); also elsewhere on the board
/3V3_SB: C398.1, C399.1, C400.1, C401.1, C402.1, R173.1, R178.1, R180.1, R192.1, U74.6 (Vs+), U75.2 (A0), U75.6 (Vs+), U76.6 (Vs+), U77.6 (Vs+), U78.1 (A1), U78.6 (Vs+); also elsewhere on the board
/5V0: C389.1, R204.2 (Vo), U67.C5 (SENSE), U68.1 (VIN), U78.8 (Vbus); also elsewhere on the board
/5V0_N: C391.1, R193.1, U68.4 (VOUT); also elsewhere on the board
/5V0_SB: R174.1, R179.1, R181.1; also elsewhere on the board
/12V0: C342.1, C343.1, C344.1, C382.1, C386.1, L7.2, U61.2 (VIN), U61.9 (SEQ/TRK), U62.2 (VIN), U62.9 (SEQ/TRK), U63.2 (VIN), U63.9 (SEQ/TRK), U65.2 (VIN), U67.A1 (VIN), U67.A2 (VIN); also elsewhere on the board
/GND: C342.2, C343.2, C344.2, C345.2, C346.2, C347.2, C348.2, C349.2, C350.2, C382.2, C383.2, C384.1, C385.2, C386.2, C387.2, C388.2, C389.2, C391.2, C392.2, C398.2, C399.2, C400.2, C401.2, C402.2, Q3.S1 (S), Q3.S2 (S), Q4.S1 (S), R175.2, R176.2, R177.2, R189.1, R190.2, R194.1, R241.2, R242.1, R243.1, U61.3 (GND), U61.7 (GND), U62.3 (GND), U62.7 (GND), U63.3 (GND), U63.7 (GND), U65.8 (PGND), U65.PAD (PGND), U66.4 (GND), U67.A3 (GND), U67.A4 (GND), U67.B1 (GND), U67.B2 (GND), U67.B3 (GND), U67.B4 (GND), U67.C2 (GND), U67.C3 (GND), U67.C4 (GND), U67.D2 (GND), U67.D3 (GND), U67.D4 (GND), U67.D5 (GND), U67.E3 (GND), U67.E4 (GND), U68.2 (GND), U68.PAD (GND), U74.1 (A1), U74.2 (A0), U74.7 (GND), U75.1 (A1), U75.7 (GND), U76.1 (A1), U76.7 (GND), U77.1 (A1), U77.7 (GND), U78.2 (A0), U78.7 (GND); also elsewhere on the board
/I2C2_SCL: U74.5 (SCL), U75.5 (SCL), U76.5 (SCL), U77.2 (A0), U77.5 (SCL), U78.5 (SCL); also elsewhere on the board
/I2C2_SDA: U74.4 (SDA), U75.4 (SDA), U76.2 (A0), U76.4 (SDA), U77.4 (SDA), U78.4 (SDA); also elsewhere on the board
/MCU/2V0_EN: Q3.G2 (G), R178.2; also elsewhere on the board
/MCU/2V0_GOOD: U62.10 (PGOOD); also elsewhere on the board
/MCU/2V5_EN: Q3.G1 (G), R173.2; also elsewhere on the board
/MCU/2V5_GOOD: U61.10 (PGOOD); also elsewhere on the board
/MCU/3V3_EN: Q4.G1 (G), R180.2; also elsewhere on the board
/MCU/3V3_GOOD: U63.10 (PGOOD); also elsewhere on the board
/MCU/5V0_EN: R243.2, U67.C1 (CTRL); also elsewhere on the board
/MCU/5V0_GOOD: R192.2, U67.D1 (PGOOD); also elsewhere on the board
/MCU/5V0_N_EN: R242.2, U68.6 (EN); also elsewhere on the board
/MCU/BACKLIGHT_PWM: U66.1 (EN); also elsewhere on the board
/MCU/VBACKLIGHT_EN: R241.1, U65.4 (EN); also elsewhere on the board
/Power Supply/Higher voltage rails/2V0_EN_SHIFT: Q3.D2 (D), R179.2, U62.1 (EN)
/Power Supply/Higher voltage rails/2V0_SENSE_HI: R201.3 (Ihi), U75.10 (Vin+)
/Power Supply/Higher voltage rails/2V0_SENSE_LO: R201.1 (Ilo), U75.9 (Vin-)
/Power Supply/Higher voltage rails/2V5_EN_SHIFT: Q3.D1 (D), R174.2, U61.1 (EN)
/Power Supply/Higher voltage rails/2V5_SENSE_HI: R200.3 (Ihi), U74.10 (Vin+)
/Power Supply/Higher voltage rails/2V5_SENSE_LO: R200.1 (Ilo), U74.9 (Vin-)
/Power Supply/Higher voltage rails/3V3_EN_SHIFT: Q4.D1 (D), R181.2, U63.1 (EN)
/Power Supply/Higher voltage rails/3V3_SENSE_HI: R202.3 (Ihi), U76.10 (Vin+)
/Power Supply/Higher voltage rails/3V3_SENSE_LO: R202.1 (Ilo), U76.9 (Vin-)
/Power Supply/Higher voltage rails/5V0_N_FB: R193.2, R194.2, U68.5 (VFB)
/Power Supply/Higher voltage rails/5V0_SENSE_HI: R204.3 (Ihi), U78.10 (Vin+)
/Power Supply/Higher voltage rails/5V0_SENSE_LO: R204.1 (Ilo), U78.9 (Vin-)
/Power Supply/Higher voltage rails/BACKLIGHT_SENSE_HI: R203.3 (Ihi), U77.10 (Vin+)
/Power Supply/Higher voltage rails/BACKLIGHT_SENSE_LO: R203.1 (Ilo), U77.9 (Vin-)
/VBACKLIGHT_N: U66.2 (OUT), U66.3 (OUT), U66.5 (OUT); also elsewhere on the board
/VBACKLIGHT_P: R188.1, R203.2 (Vo), U77.8 (Vbus); also elsewhere on the board
unnamed: C345.1, C348.1, R200.4 (Vi), U61.4 (VOUT)
unnamed: C346.1, C349.1, R201.4 (Vi), U62.4 (VOUT)
unnamed: C347.1, C350.1, R202.4 (Vi), U63.4 (VOUT)
unnamed: C383.1, U65.3 (VDD)
unnamed: C384.2, U65.5 (SS)
unnamed: C385.1, R203.4 (Vi), U65.1 (VOUT)
unnamed: C387.1, C388.1, R204.4 (Vi), U67.A5 (VOUT), U67.B5 (VOUT)
unnamed: C390.1, U68.8 (C1+)
unnamed: C390.2, U68.7 (C1-)
unnamed: C392.1, U68.3 (CPOUT)
unnamed: L7.1, U65.7 (SW)
unnamed: R175.1, U61.6 (TRIM)
unnamed: R176.1, U62.6 (TRIM)
unnamed: R177.1, U63.6 (TRIM)
unnamed: R188.2, R189.2, U65.6 (FB)
unnamed: R190.1, U66.6 (REXT)

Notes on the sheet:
Vout = 1.25V * (R1/R2 + 1) R2 <= 1K R1 = 16.2K
We want a total of ~~40 mA Backlight Vf is 17.4 - 19.8V @ 20 mA Rext = Vdrop / (Iout - (Vdrop / Rint)) 40 ohms gives 33.75 mA Max 1W inst power, 150C, 225 C/W Worst case Vf = 17.4V, dropping 4.1V = 138 mW, 31.05C rise Best case 19.8V, dropping 1.7V = 58 mW, 13C rise
Target -4.75V to provide LDO headroom We don't need exactly -5.0 Vout =-1.22 * (R1+R2)/R2, R2 >= 50K R2 = 100K R1 = 289K
8'h80
8'h82
8'h84
8'h86
8'h88
12 mR = 12 mV @ 1A 208.333 uA/LSB
12 mR = 6 mV @ 0.5A 208.333 uA/LSB
12 mR = 36 mV @ 3A 208.333 uA/LSB
100 mR = 4 mV @ 40 mA 25 uA/LSB
100 mR = 10 mV @ 100 mA 25 uA/LSB
16 bits signed, 81.92 mV full scale 2.5 uV/LSB
All rails here are max 3A LVK12 is rated for 500 mW 3A through 12 mR is 108 mW
